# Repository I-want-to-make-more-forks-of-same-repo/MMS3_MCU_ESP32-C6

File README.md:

# MMS 3 ESP32 C6

## Project Status: **Ongoing**  
### Ver 1.0
**Design** ✅ — **Fabrication** ⏳ — **Assembly** ⏳ — **Bringup** ⏳ — **Testing** ⏳

Jak za 3 razem się udało, to za 4 też będzie git!

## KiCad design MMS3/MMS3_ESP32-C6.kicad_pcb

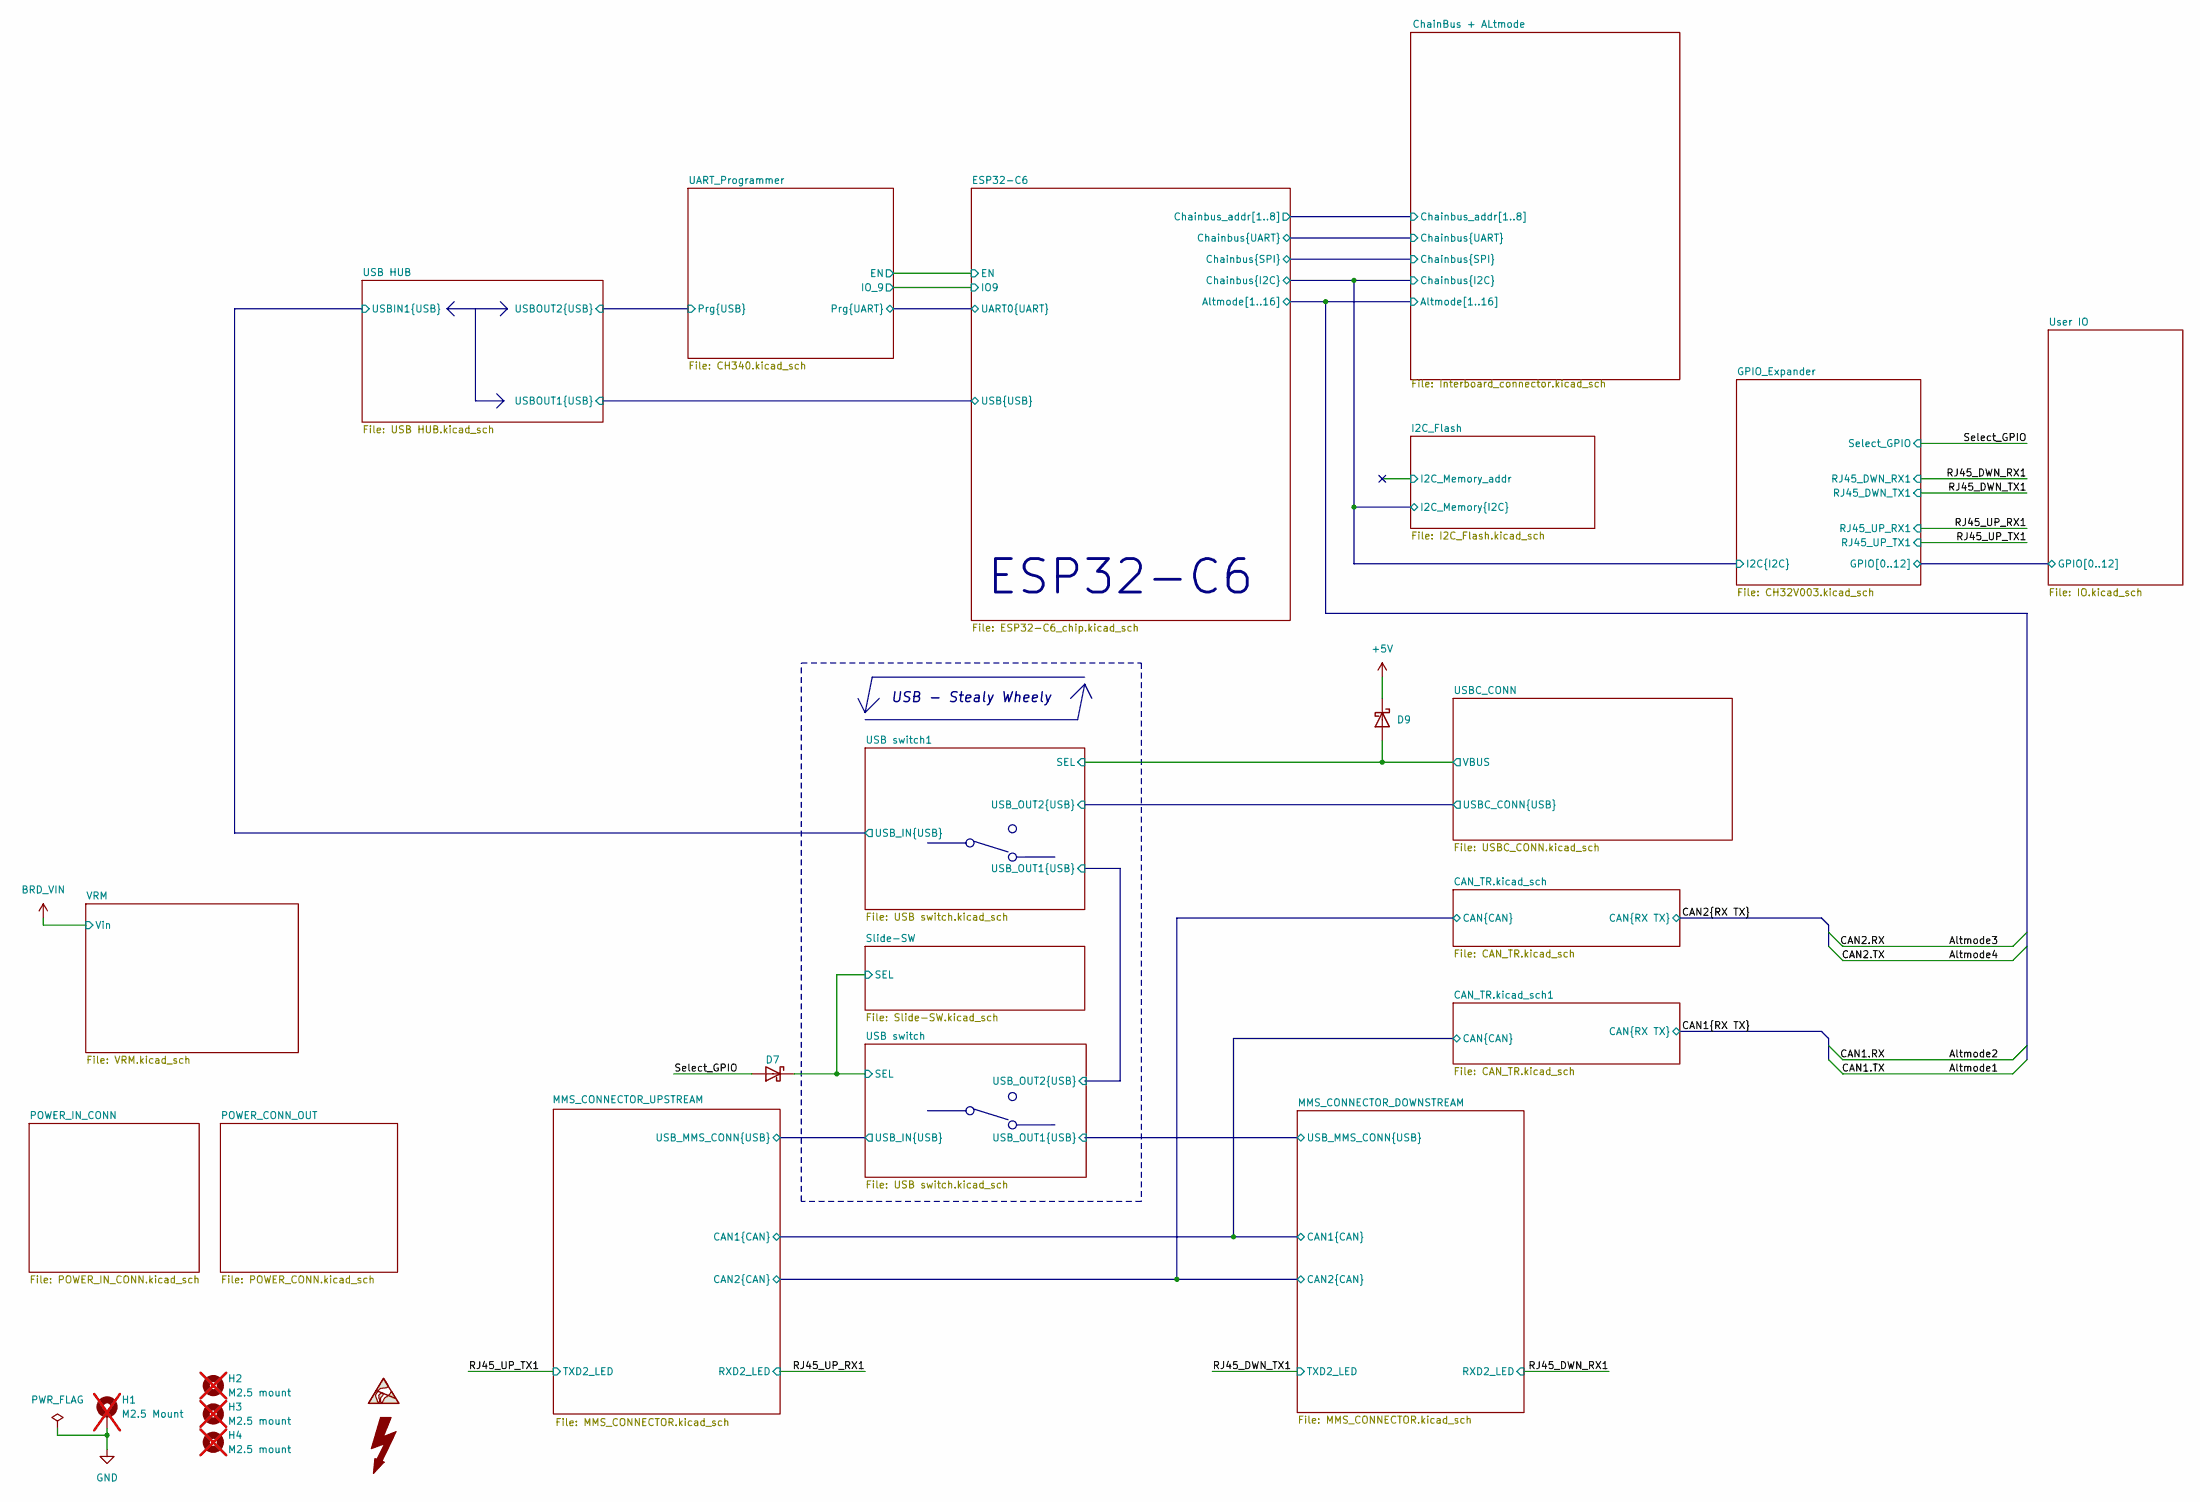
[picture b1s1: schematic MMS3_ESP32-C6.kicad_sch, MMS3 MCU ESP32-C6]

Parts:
D7, D9: 1N5819WS; D_SOD-323; Forward Voltage (Vf@If) 600mV@1A; Reverse Voltage (Vr) 40V; Part 1N5819WS; LCSC C191023
H1: M2.5 Mount; MountingHole_2.7mm_M2.5_DIN965_Pad_TopOnly; not fitted
H2, H3, H4: M2.5 mount; MountingHole_2.7mm_M2.5; not fitted

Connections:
+5V: D9.1; also elsewhere on the board
/Select_GPIO: D7.2; also elsewhere on the board
/Slide-SW/SEL: D7.1; also elsewhere on the board
/USBC_CONN/VBUS: D9.2; also elsewhere on the board
GND: H1.1 (1_1); also elsewhere on the board

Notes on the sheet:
USB - Stealy Wheely
ESP32-C6

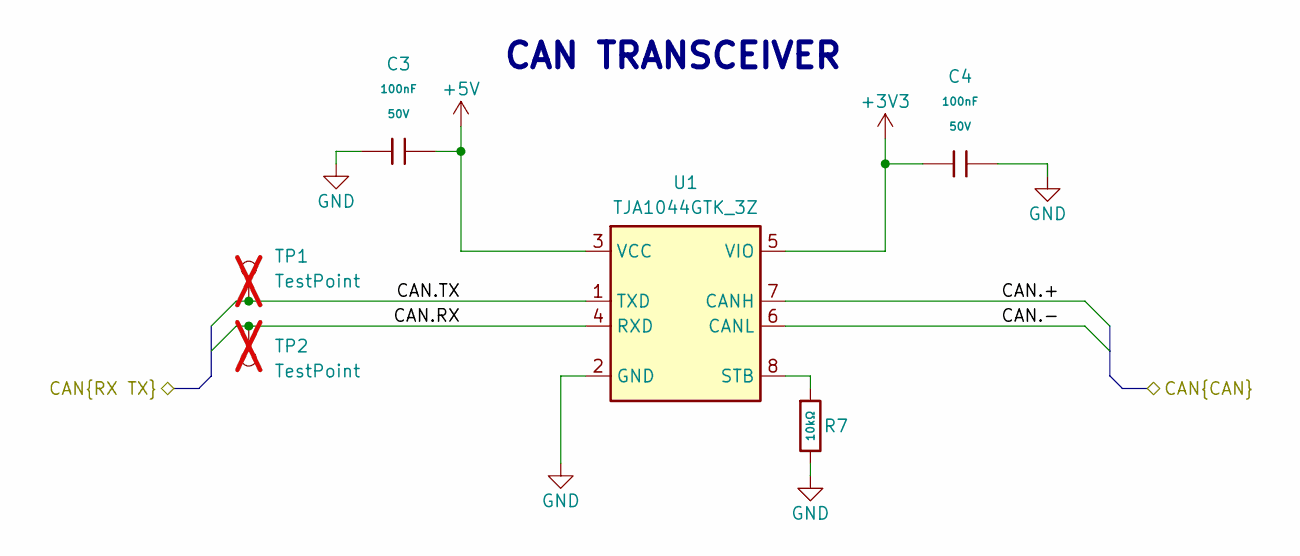
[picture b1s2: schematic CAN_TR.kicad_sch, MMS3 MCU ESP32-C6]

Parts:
C3, C4: 100nF; C_0402; Voltage Rated 50V; Tolerance ±10%; Part CL05B104KB54PNC; LCSC C307331
R7: 10kΩ; R_0402; Overload Voltage (Max) 50V; Tolerance ±1%; Part 0402WGF1002TCE; LCSC C25744
TP1, TP2: TestPoint; TestPoint_Pad_D1.0mm; not fitted
U1: TJA1044GTK_3Z; HVSON-8-1EP_3x3mm_P0.65mm_EP1.6x2.4mm; Manufacturer_Part_Number TJA1044GTK/3Z; LCSC C5215851

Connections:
+3V3: C4.1, U1.5 (VIO); also elsewhere on the board
+5V: C3.2, U1.3 (VCC); also elsewhere on the board
/CAN_TR.kicad_sch/CAN.+: U1.7 (CANH); also elsewhere on the board
/CAN_TR.kicad_sch/CAN.-: U1.6 (CANL); also elsewhere on the board
/ChainBus + ALtmode/Altmode3: TP2.1 (1_1), U1.4 (RXD); also elsewhere on the board
/ChainBus + ALtmode/Altmode4: TP1.1 (1_1), U1.1 (TXD); also elsewhere on the board
GND: C3.1, C4.2, R7.2, U1.2 (GND), U1.9 (EP); also elsewhere on the board
unnamed: R7.1, U1.8 (STB)

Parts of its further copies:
C6, C7: 100nF; C_0402; Voltage Rated 50V; Tolerance ±10%; Part CL05B104KB54PNC; LCSC C307331
R12: 10kΩ; R_0402; Overload Voltage (Max) 50V; Tolerance ±1%; Part 0402WGF1002TCE; LCSC C25744
TP3, TP4: TestPoint; TestPoint_Pad_D1.0mm; not fitted
U6: TJA1044GTK_3Z; HVSON-8-1EP_3x3mm_P0.65mm_EP1.6x2.4mm; Manufacturer_Part_Number TJA1044GTK/3Z; LCSC C5215851

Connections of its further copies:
+3V3: C7.1, U6.5 (VIO); also elsewhere on the board
+5V: C6.2, U6.3 (VCC); also elsewhere on the board
/CAN_TR.kicad_sch1/CAN.+: U6.7 (CANH); also elsewhere on the board
/CAN_TR.kicad_sch1/CAN.-: U6.6 (CANL); also elsewhere on the board
/ChainBus + ALtmode/Altmode1: TP3.1 (1_1), U6.1 (TXD); also elsewhere on the board
/ChainBus + ALtmode/Altmode2: TP4.1 (1_1), U6.4 (RXD); also elsewhere on the board
GND: C6.1, C7.2, R12.2, U6.2 (GND), U6.9 (EP); also elsewhere on the board
unnamed: R12.1, U6.8 (STB)

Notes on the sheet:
CAN TRANSCEIVER

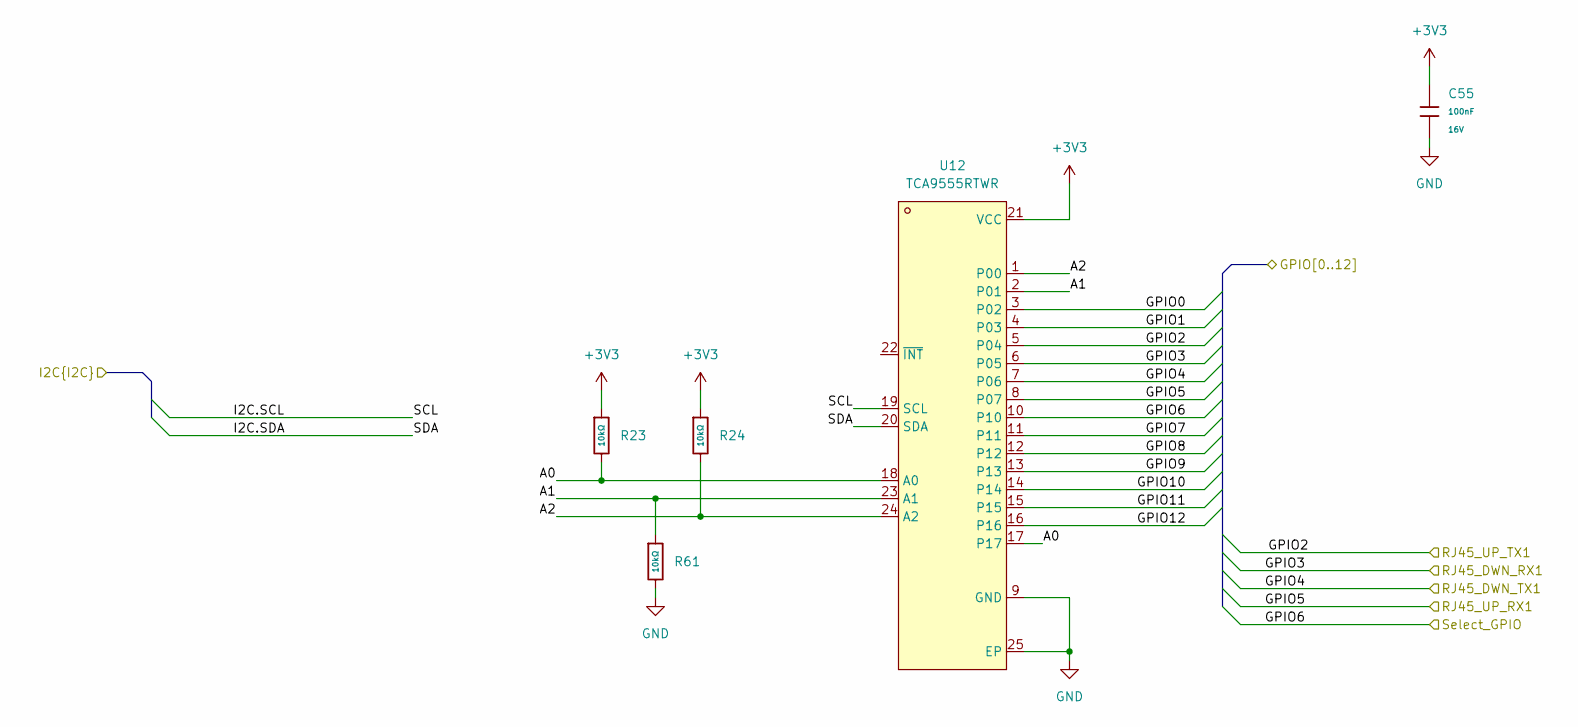
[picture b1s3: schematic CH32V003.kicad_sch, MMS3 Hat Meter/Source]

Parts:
C55: 100nF; C_0402; Voltage Rated 16V; Tolerance ±10%; Part CL05B104KO5NNNC; LCSC C1525
R23, R24, R61: 10kΩ; R_0402; Overload Voltage (Max) 50V; Tolerance ±1%; Part 0402WGF1002TCE; LCSC C25744
U12: TCA9555RTWR; HVQFN-24_L4.0-W4.0-P0.50-BL-EP2.6; MPN TCA9555RTWR(UMW); LCSC Part C42420609

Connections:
+3V3: C55.1, R23.1, R24.1, U12.21 (VCC); also elsewhere on the board
/ChainBus + ALtmode/Chainbus.SCL: U12.19 (SCL); also elsewhere on the board
/ChainBus + ALtmode/Chainbus.SDA: U12.20 (SDA); also elsewhere on the board
/GPIO_Expander/A0: R23.2, U12.17, U12.18 (A0)
/GPIO_Expander/A1: R61.1, U12.2 (P01), U12.23 (A1)
/GPIO_Expander/A2: R24.2, U12.1 (P00), U12.24 (A2)
/GPIO_Expander/GPIO0: U12.3 (P02); also elsewhere on the board
/GPIO_Expander/GPIO1: U12.4 (P03); also elsewhere on the board
/GPIO_Expander/GPIO7: U12.11
/GPIO_Expander/GPIO8: U12.12; also elsewhere on the board
/GPIO_Expander/GPIO9: U12.13; also elsewhere on the board
/GPIO_Expander/GPIO10: U12.14; also elsewhere on the board
/GPIO_Expander/GPIO11: U12.15
/GPIO_Expander/GPIO12: U12.16
/RJ45_DWN_RX1: U12.6 (P05); also elsewhere on the board
/RJ45_DWN_TX1: U12.7 (P06); also elsewhere on the board
/RJ45_UP_RX1: U12.8 (P07); also elsewhere on the board
/RJ45_UP_TX1: U12.5 (P04); also elsewhere on the board
/Select_GPIO: U12.10; also elsewhere on the board
GND: C55.2, R61.2, U12.9 (GND), U12.25 (EP); also elsewhere on the board

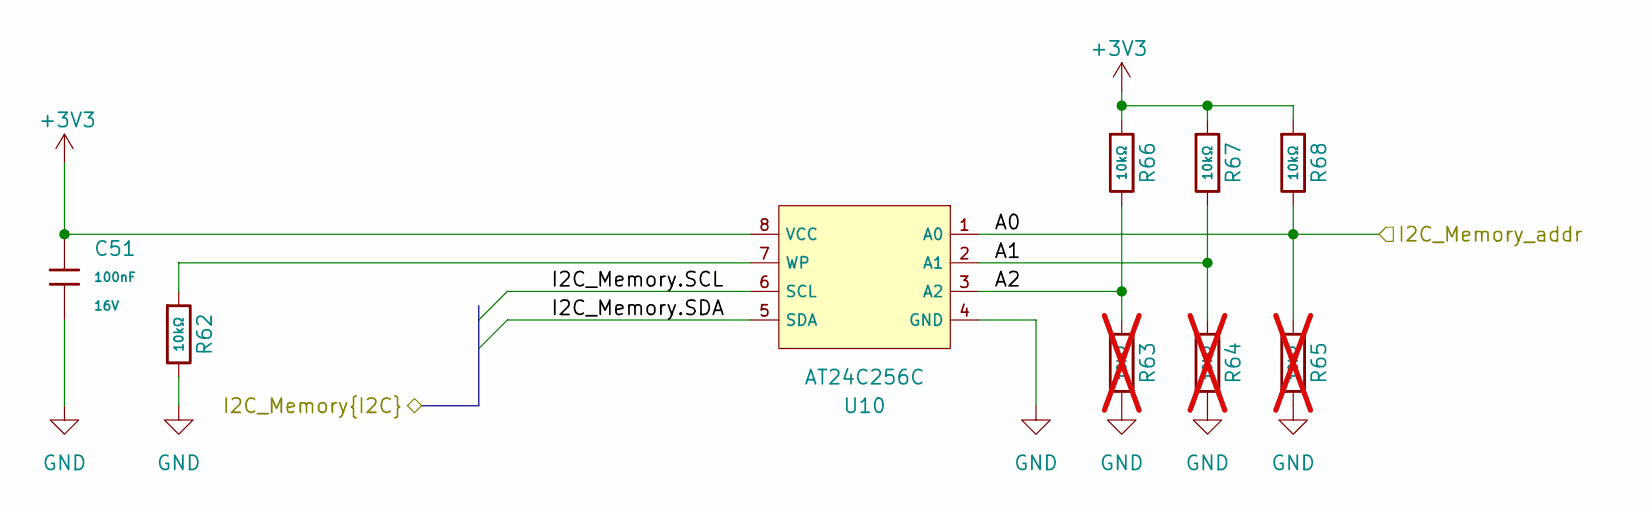
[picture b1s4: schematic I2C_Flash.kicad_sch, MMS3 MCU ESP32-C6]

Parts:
C51: 100nF; C_0402; Voltage Rated 16V; Tolerance ±10%; Part CL05B104KO5NNNC; LCSC C1525
R62, R66, R67, R68: 10kΩ; R_0402; Overload Voltage (Max) 50V; Tolerance ±1%; Part 0402WGF1002TCE; LCSC C25744
R63, R64, R65: 10kΩ; R_0402; Overload Voltage (Max) 50V; Tolerance ±1%; Part 0402WGF1002TCE; LCSC C25744; not fitted
U10: AT24C256C; SOIC-8_5.3x5.3mm_P1.27mm; Supply Voltage 1.7V~5.5V; Part AT24C256C-SSHL-T; LCSC C6482

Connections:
+3V3: C51.1, R66.1, R67.1, R68.1, U10.8 (VCC); also elsewhere on the board
/ChainBus + ALtmode/Chainbus.SCL: U10.6 (SCL); also elsewhere on the board
/ChainBus + ALtmode/Chainbus.SDA: U10.5 (SDA); also elsewhere on the board
/I2C_Flash/A0: R65.1, R68.2, U10.1 (A0)
/I2C_Flash/A1: R64.1, R67.2, U10.2 (A1)
/I2C_Flash/A2: R63.1, R66.2, U10.3 (A2)
GND: C51.2, R62.2, R63.2, R64.2, R65.2, U10.4 (GND); also elsewhere on the board
unnamed: R62.1, U10.7 (WP)

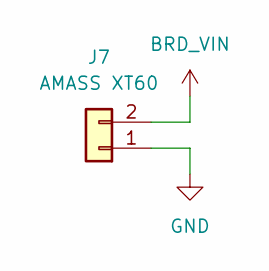
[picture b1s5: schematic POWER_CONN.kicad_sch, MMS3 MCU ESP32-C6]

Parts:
J7: AMASS XT60; AMASS_XT60PW-F_1x02_P7.20mm_Horizontal; LCSC C428722

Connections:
BRD_VIN: J7.2; also elsewhere on the board
GND: J7.1; also elsewhere on the board

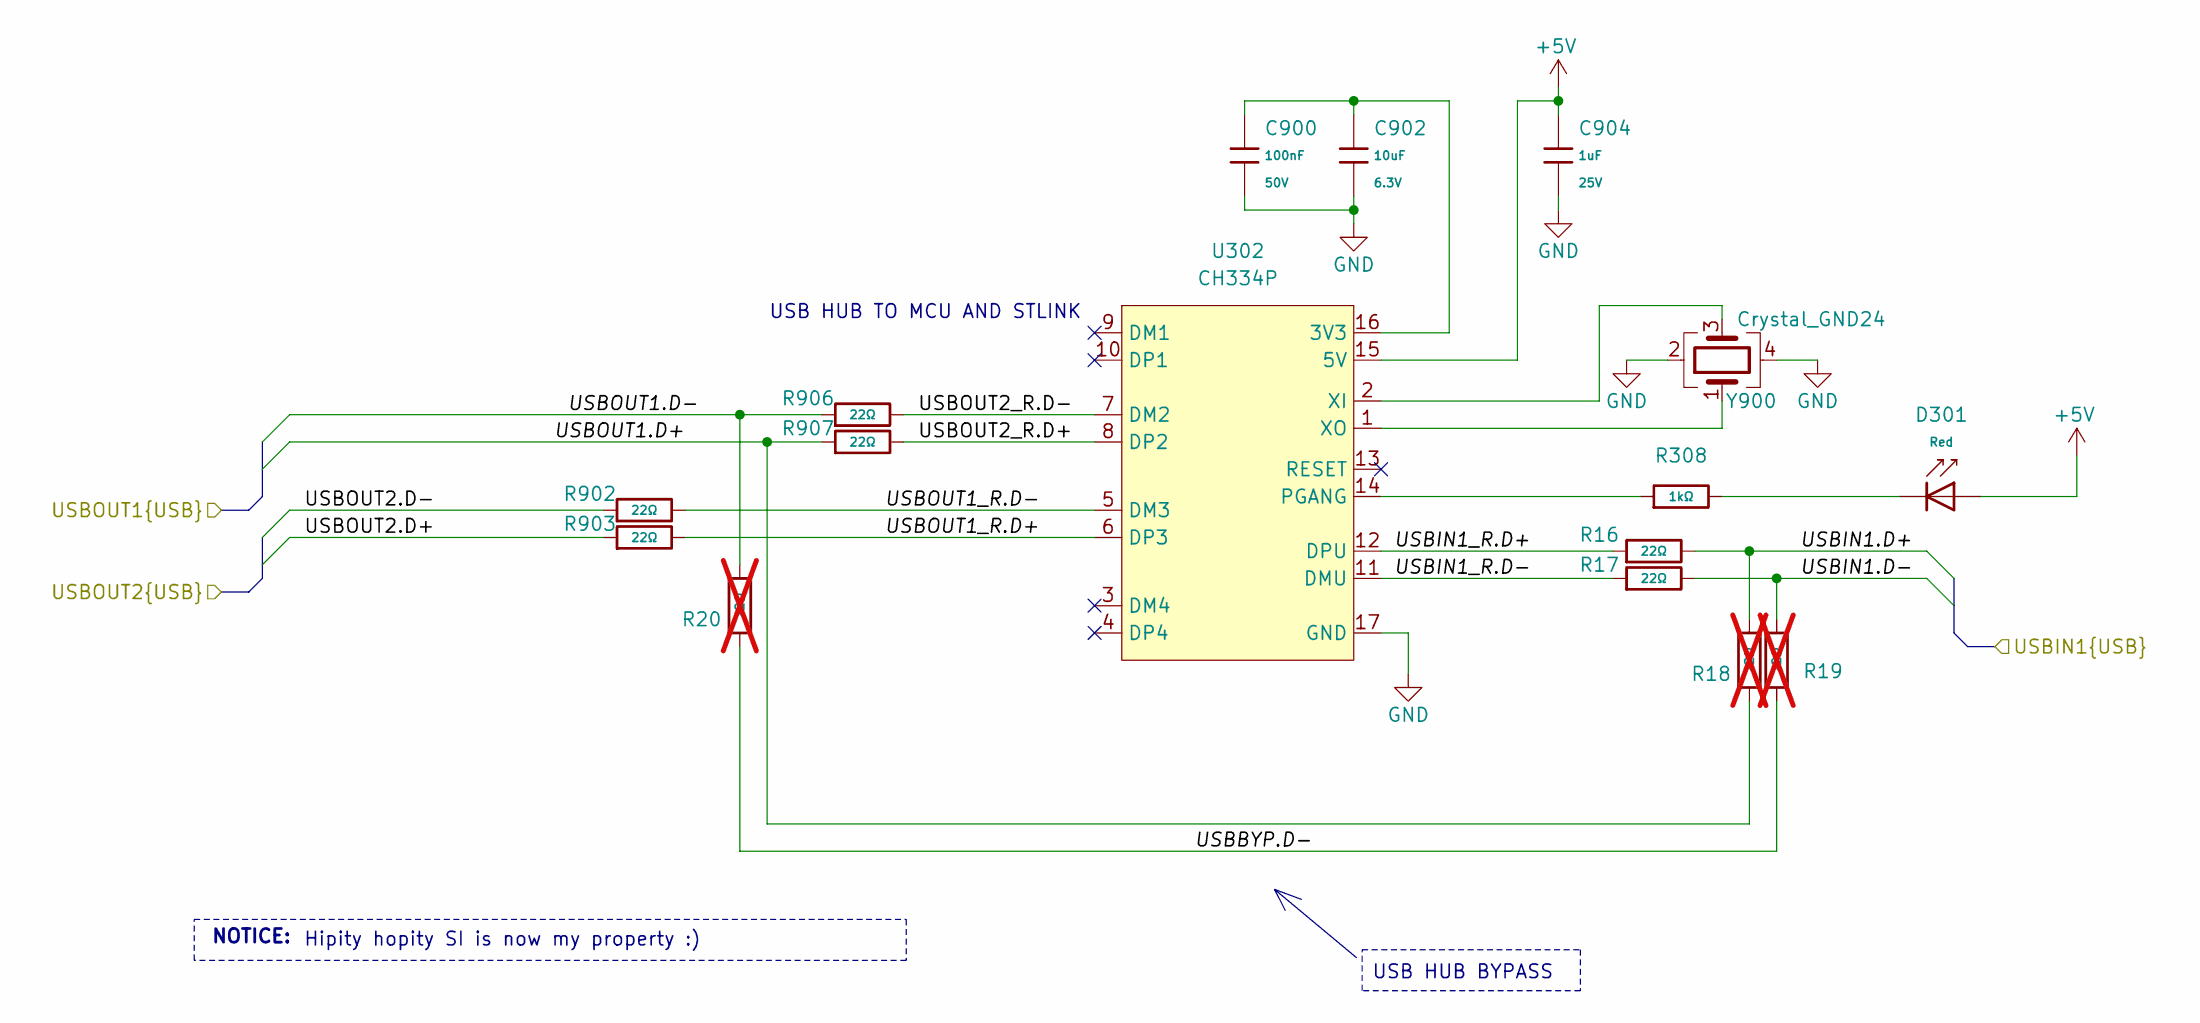
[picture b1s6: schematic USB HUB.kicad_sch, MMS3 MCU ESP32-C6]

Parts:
C900: 100nF; C_0402; Voltage Rated 50V; Tolerance ±10%; Part CL05B104KB54PNC; LCSC C307331
C902: 10uF; C_0402; Voltage Rated 6.3V; Tolerance ±20%; Part CL05A106MQ5NUNC; LCSC C15525
C904: 1uF; C_0402; Voltage Rated 25V; Tolerance ±10%; Part CL05A105KA5NQNC; LCSC C52923
D301: Red; D_0603; Part KT-0603R; LCSC C2286
R16, R17, R902, R903, R906, R907: 22Ω; R_0402; Overload Voltage (Max) 50V; Tolerance ±1%; Part 0402WGF220JTCE; LCSC C25092
R18, R19, R20: 22Ω; R_0402; Overload Voltage (Max) 50V; Tolerance ±1%; Part 0402WGF220JTCE; LCSC C25092; not fitted
R308: 1kΩ; R_0402; Overload Voltage (Max) 50V; Tolerance ±1%; Part 0402WGF1001TCE; LCSC C11702
U302: CH334P; QFN-16-1EP_3x3mm_P0.5mm_EP1.7x1.7mm; LCSC C5373042
Y900: Crystal_GND24; Crystal_SMD_3225-4Pin_3.2x2.5mm; LCSC C9002

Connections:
+5V: C904.1, D301.2, U302.15 (5V); also elsewhere on the board
/ESP32-C6/USB.D+: R18.1, R907.1; also elsewhere on the board
/ESP32-C6/USB.D-: R20.2, R906.1; also elsewhere on the board
/UART_Programmer/Prg.D+: R903.1; also elsewhere on the board
/UART_Programmer/Prg.D-: R902.1; also elsewhere on the board
/USB HUB/USBBYP.D-: R19.1, R20.1
/USB HUB/USBIN1.D+: R16.2, R18.2; also elsewhere on the board
/USB HUB/USBIN1.D-: R17.2, R19.2; also elsewhere on the board
/USB HUB/USBIN1_R.D+: R16.1, U302.12 (DPU)
/USB HUB/USBIN1_R.D-: R17.1, U302.11 (DMU)
/USB HUB/USBOUT1_R.D+: R903.2, U302.6 (DP3)
/USB HUB/USBOUT1_R.D-: R902.2, U302.5 (DM3)
/USB HUB/USBOUT2_R.D+: R907.2, U302.8 (DP2)
/USB HUB/USBOUT2_R.D-: R906.2, U302.7 (DM2)
GND: C900.2, C902.2, C904.2, U302.17 (GND), Y900.2, Y900.4; also elsewhere on the board
unnamed: D301.1, R308.2
unnamed: C900.1, C902.1, U302.16 (3V3)
unnamed: R308.1, U302.14 (PGANG)
unnamed: U302.2 (XI), Y900.3
unnamed: U302.1 (XO), Y900.1

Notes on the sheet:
NOTICE:
Hipity hopity SI is now my property :)
USB HUB TO MCU AND STLINK
USB HUB BYPASS

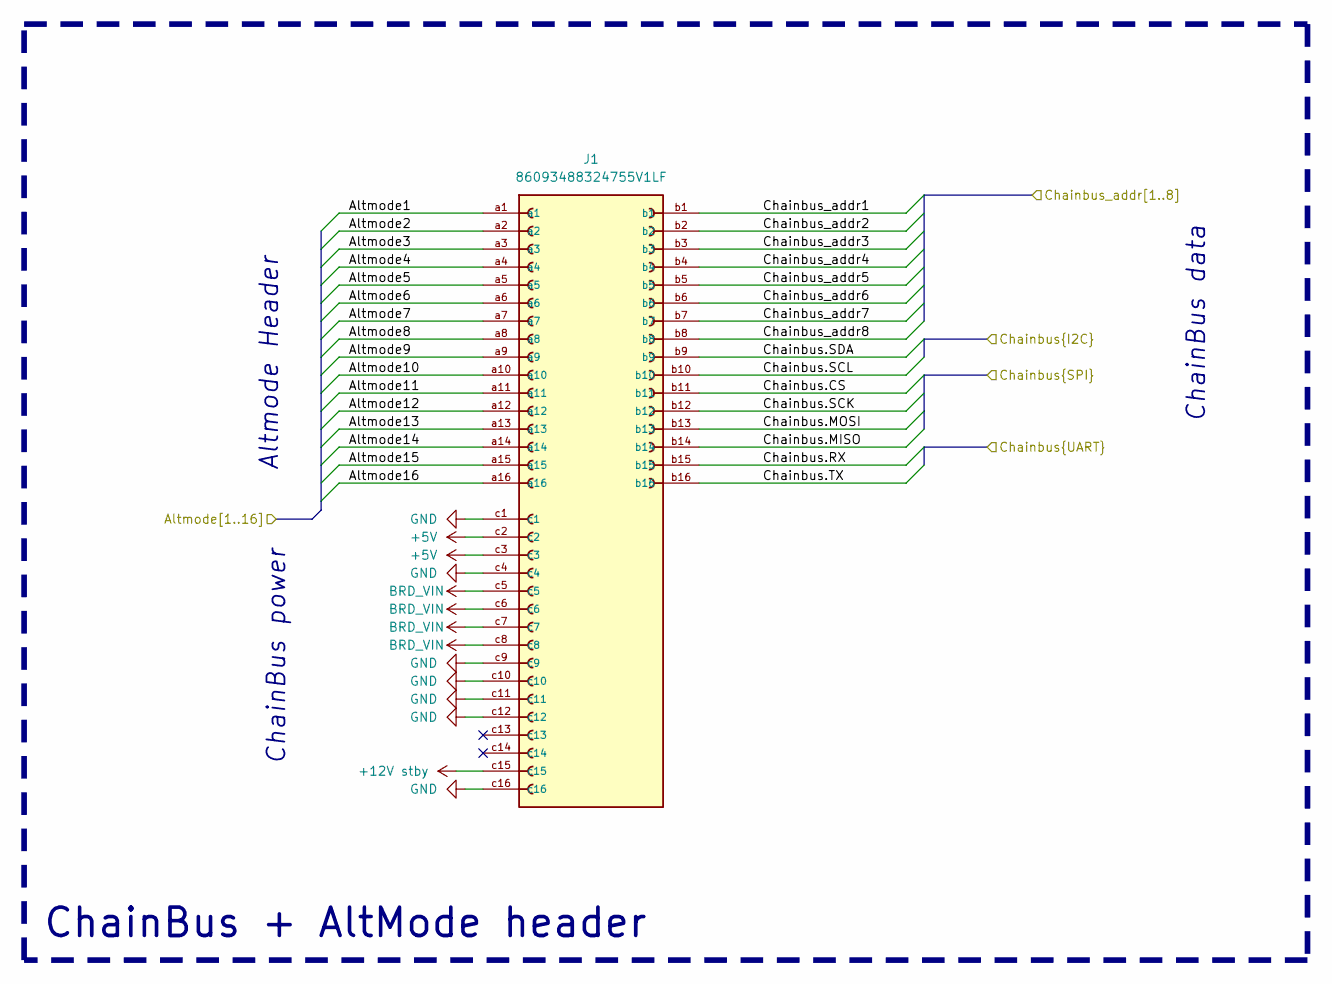
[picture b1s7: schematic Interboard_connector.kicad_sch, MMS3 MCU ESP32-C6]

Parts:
J1: 86093488324755V1LF; DIN41612_C2_3x16_Female_Vertical_THT; PARTREV C; LCSC C5173373

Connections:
+5V: J1.c2, J1.c3; also elsewhere on the board
+12V stby: J1.c15; also elsewhere on the board
/ChainBus + ALtmode/Altmode1: J1.a1; also elsewhere on the board
/ChainBus + ALtmode/Altmode2: J1.a2; also elsewhere on the board
/ChainBus + ALtmode/Altmode3: J1.a3; also elsewhere on the board
/ChainBus + ALtmode/Altmode4: J1.a4; also elsewhere on the board
/ChainBus + ALtmode/Altmode5: J1.a5
/ChainBus + ALtmode/Altmode6: J1.a6
/ChainBus + ALtmode/Altmode7: J1.a7
/ChainBus + ALtmode/Altmode8: J1.a8
/ChainBus + ALtmode/Altmode9: J1.a9
/ChainBus + ALtmode/Altmode10: J1.a10
/ChainBus + ALtmode/Altmode11: J1.a11
/ChainBus + ALtmode/Altmode12: J1.a12
/ChainBus + ALtmode/Altmode13: J1.a13
/ChainBus + ALtmode/Altmode14: J1.a14
/ChainBus + ALtmode/Altmode15: J1.a15
/ChainBus + ALtmode/Altmode16: J1.a16
/ChainBus + ALtmode/Chainbus.CS: J1.b11; also elsewhere on the board
/ChainBus + ALtmode/Chainbus.MISO: J1.b14; also elsewhere on the board
/ChainBus + ALtmode/Chainbus.MOSI: J1.b13; also elsewhere on the board
/ChainBus + ALtmode/Chainbus.RX: J1.b15; also elsewhere on the board
/ChainBus + ALtmode/Chainbus.SCK: J1.b12; also elsewhere on the board
/ChainBus + ALtmode/Chainbus.SCL: J1.b10; also elsewhere on the board
/ChainBus + ALtmode/Chainbus.SDA: J1.b9; also elsewhere on the board
/ChainBus + ALtmode/Chainbus.TX: J1.b16; also elsewhere on the board
/ChainBus + ALtmode/Chainbus_addr1: J1.b1; also elsewhere on the board
/ChainBus + ALtmode/Chainbus_addr2: J1.b2; also elsewhere on the board
/ChainBus + ALtmode/Chainbus_addr3: J1.b3; also elsewhere on the board
/ChainBus + ALtmode/Chainbus_addr4: J1.b4; also elsewhere on the board
/ChainBus + ALtmode/Chainbus_addr5: J1.b5; also elsewhere on the board
/ChainBus + ALtmode/Chainbus_addr6: J1.b6; also elsewhere on the board
/ChainBus + ALtmode/Chainbus_addr7: J1.b7; also elsewhere on the board
/ChainBus + ALtmode/Chainbus_addr8: J1.b8; also elsewhere on the board
BRD_VIN: J1.c5, J1.c6, J1.c7, J1.c8; also elsewhere on the board
GND: J1.c1, J1.c4, J1.c9, J1.c10, J1.c11, J1.c12, J1.c16; also elsewhere on the board

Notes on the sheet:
ChainBus data
ChainBus power
Altmode Header
ChainBus + AltMode header

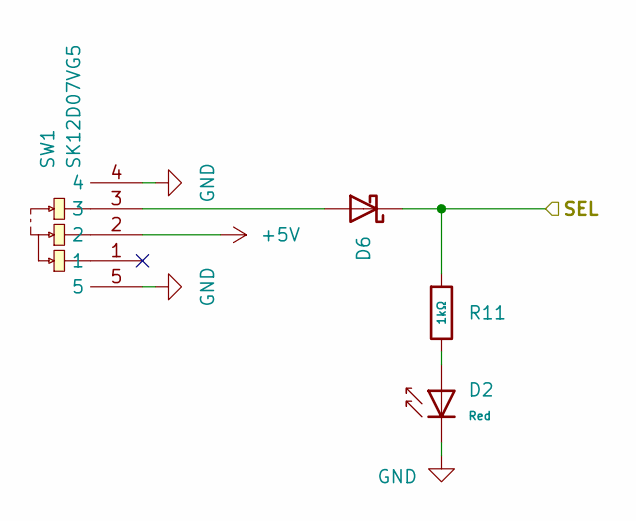
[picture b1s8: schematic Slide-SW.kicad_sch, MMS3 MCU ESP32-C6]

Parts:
D2: Red; D_0603; Part KT-0603R; LCSC C2286
D6: 1N5819WS; D_SOD-323; Forward Voltage (Vf@If) 600mV@1A; Reverse Voltage (Vr) 40V; Part 1N5819WS; LCSC C191023
R11: 1kΩ; R_0402; Overload Voltage (Max) 50V; Tolerance ±1%; Part 0402WGF1001TCE; LCSC C11702
SW1: SK12D07VG5; SW-TH_SK12D07VG5-1; MPN SK12D07VG5; LCSC Part C431548

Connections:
+5V: SW1.2; also elsewhere on the board
/Slide-SW/SEL: D6.1, R11.1; also elsewhere on the board
GND: D2.1, SW1.4, SW1.5; also elsewhere on the board
unnamed: D2.2, R11.2
unnamed: D6.2, SW1.3

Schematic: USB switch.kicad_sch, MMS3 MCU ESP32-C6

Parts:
C5: 100nF; C_0402; Voltage Rated 50V; Tolerance ±10%; Part CL05B104KB54PNC; LCSC C307331
R8, R10: 10kΩ; R_0402; Overload Voltage (Max) 50V; Tolerance ±1%; Part 0402WGF1002TCE; LCSC C25744
R9: 22kΩ; R_0402; Overload Voltage (Max) 50V; Tolerance ±1%; Part 0402WGF2202TCE; LCSC C25768
U3: FSUSB42UMX; UQFN-10_1.4x1.8mm_P0.4mm; PARTREV 1.25; LCSC C11145

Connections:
+3V3: C5.1, U3.9 (VCC); also elsewhere on the board
/MMS_CONNECTOR_DOWNSTREAM/USB_MMS_CONN.D+: U3.5 (HSD1+); also elsewhere on the board
/MMS_CONNECTOR_DOWNSTREAM/USB_MMS_CONN.D-: U3.4 (HSD1-); also elsewhere on the board
/MMS_CONNECTOR_UPSTREAM/USB_MMS_CONN.D+: U3.1 (D+); also elsewhere on the board
/MMS_CONNECTOR_UPSTREAM/USB_MMS_CONN.D-: U3.2 (D-); also elsewhere on the board
/Slide-SW/SEL: R8.1; also elsewhere on the board
/USB switch/USB_OUT2.D+: U3.7 (HSD2+); also elsewhere on the board
/USB switch/USB_OUT2.D-: U3.6 (HSD2-); also elsewhere on the board
GND: C5.2, R9.2, R10.2, U3.3 (GND); also elsewhere on the board
unnamed: R8.2, R9.1, U3.10 (SEL)
unnamed: R10.1, U3.8 (~OE)

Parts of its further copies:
C8: 100nF; C_0402; Voltage Rated 50V; Tolerance ±10%; Part CL05B104KB54PNC; LCSC C307331
R13, R15: 10kΩ; R_0402; Overload Voltage (Max) 50V; Tolerance ±1%; Part 0402WGF1002TCE; LCSC C25744
R14: 22kΩ; R_0402; Overload Voltage (Max) 50V; Tolerance ±1%; Part 0402WGF2202TCE; LCSC C25768
U7: FSUSB42UMX; UQFN-10_1.4x1.8mm_P0.4mm; PARTREV 1.25; LCSC C11145

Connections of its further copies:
+3V3: C8.1, U7.9 (VCC); also elsewhere on the board
/USB HUB/USBIN1.D+: U7.1 (D+); also elsewhere on the board
/USB HUB/USBIN1.D-: U7.2 (D-); also elsewhere on the board
/USB switch1/USB_OUT2.D+: U7.7 (HSD2+); also elsewhere on the board
/USB switch1/USB_OUT2.D-: U7.6 (HSD2-); also elsewhere on the board
/USB switch/USB_OUT2.D+: U7.5 (HSD1+); also elsewhere on the board
/USB switch/USB_OUT2.D-: U7.4 (HSD1-); also elsewhere on the board
/USBC_CONN/VBUS: R13.1; also elsewhere on the board
GND: C8.2, R14.2, R15.2, U7.3 (GND); also elsewhere on the board
unnamed: R13.2, R14.1, U7.10 (SEL)
unnamed: R15.1, U7.8 (~OE)

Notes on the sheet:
ALTERNATE PART: EnergyMath EMS3900 1.9Ω 800MHz 2:1 USB QFN-10L(1.4x1.8) Analog Switches - Special Purpose ROHS PIN COMPATIBLE
NOTE:

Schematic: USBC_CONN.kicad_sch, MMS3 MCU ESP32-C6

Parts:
C12: 100nF; C_0402; Voltage Rated 16V; Tolerance ±10%; Part CL05B104KO5NNNC; LCSC C1525
C13: 10nF; C_0402; Voltage Rated 50V; Tolerance ±10%; Part CL05B103KB5NNNC; LCSC C15195
J4: USB_C_Receptacle_USB2.0_16P; USB_C_Receptacle_GCT_USB4105-xx-A_16P_TopMnt_Horizontal; LCSC C165948
R25, R26: 5.1kΩ; R_0402; Overload Voltage (Max) 50V; Tolerance ±1%; Part 0402WGF5101TCE; LCSC C25905
R27: 33kΩ; R_0402; Overload Voltage (Max) 50V; Tolerance ±1%; Part 0402WGF3302TCE; LCSC C25779
U9: TPD2EUSB30DRTR-TP; SOT-723; LCSC C2844720

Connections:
/USB switch1/USB_OUT2.D+: J4.A6 (D+), J4.B6 (D+), U9.2; also elsewhere on the board
/USB switch1/USB_OUT2.D-: J4.A7 (D-), J4.B7 (D-), U9.1; also elsewhere on the board
/USBC_CONN/CC1: J4.A5 (CC1), R25.1
/USBC_CONN/CC2: J4.B5 (CC2), R26.1
/USBC_CONN/VBUS: C12.1, J4.A4 (VBUS), J4.A9 (VBUS), J4.B4 (VBUS), J4.B9 (VBUS); also elsewhere on the board
GND: C12.2, C13.2, J4.A1 (GND), J4.A12 (GND), J4.B1 (GND), J4.B12 (GND), R25.2, R26.2, R27.2, U9.3; also elsewhere on the board
unnamed: C13.1, J4.SH (SHIELD), R27.1

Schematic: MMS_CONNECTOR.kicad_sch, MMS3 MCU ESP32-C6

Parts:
C1: 10nF; C_0402; Voltage Rated 50V; Tolerance ±10%; Part CL05B103KB5NNNC; LCSC C15195
J8: RJ45_LED_Shielded; RJ45_Amphenol_RJHSE538X; LCSC C7501824; not fitted
R1, R3: 220Ω; R_0402; Overload Voltage (Max) 50V; Tolerance ±1%; Part 0402WGF2200TCE; LCSC C25091
R5: 33kΩ; R_0402; Overload Voltage (Max) 50V; Tolerance ±1%; Part 0402WGF3302TCE; LCSC C25779
U4: TPD2EUSB30DRTR-TP; SOT-723; LCSC C2844720

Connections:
+12V stby: J8.6; also elsewhere on the board
/CAN_TR.kicad_sch1/CAN.+: J8.2; also elsewhere on the board
/CAN_TR.kicad_sch1/CAN.-: J8.1; also elsewhere on the board
/CAN_TR.kicad_sch/CAN.+: J8.5; also elsewhere on the board
/CAN_TR.kicad_sch/CAN.-: J8.4; also elsewhere on the board
/MMS_CONNECTOR_DOWNSTREAM/USB_MMS_CONN.D+: J8.8, U4.2; also elsewhere on the board
/MMS_CONNECTOR_DOWNSTREAM/USB_MMS_CONN.D-: J8.7, U4.1; also elsewhere on the board
/RJ45_DWN_RX1: R3.2; also elsewhere on the board
/RJ45_DWN_TX1: R1.2; also elsewhere on the board
GND: C1.2, J8.3, J8.9, J8.11, R5.2, U4.3; also elsewhere on the board
unnamed: C1.1, J8.SH, R5.1
unnamed: J8.10, R1.1
unnamed: J8.12, R3.1

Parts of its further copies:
C2: 10nF; C_0402; Voltage Rated 50V; Tolerance ±10%; Part CL05B103KB5NNNC; LCSC C15195
J9: RJ45_LED_Shielded; RJ45_Amphenol_RJHSE538X; LCSC C7501824; not fitted
R2, R4: 220Ω; R_0402; Overload Voltage (Max) 50V; Tolerance ±1%; Part 0402WGF2200TCE; LCSC C25091
R6: 33kΩ; R_0402; Overload Voltage (Max) 50V; Tolerance ±1%; Part 0402WGF3302TCE; LCSC C25779
U5: TPD2EUSB30DRTR-TP; SOT-723; LCSC C2844720

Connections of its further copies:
+12V stby: J9.6; also elsewhere on the board
/CAN_TR.kicad_sch1/CAN.+: J9.2; also elsewhere on the board
/CAN_TR.kicad_sch1/CAN.-: J9.1; also elsewhere on the board
/CAN_TR.kicad_sch/CAN.+: J9.5; also elsewhere on the board
/CAN_TR.kicad_sch/CAN.-: J9.4; also elsewhere on the board
/MMS_CONNECTOR_UPSTREAM/USB_MMS_CONN.D+: J9.8, U5.2; also elsewhere on the board
/MMS_CONNECTOR_UPSTREAM/USB_MMS_CONN.D-: J9.7, U5.1; also elsewhere on the board
/RJ45_UP_RX1: R4.2; also elsewhere on the board
/RJ45_UP_TX1: R2.2; also elsewhere on the board
GND: C2.2, J9.3, J9.9, J9.11, R6.2, U5.3; also elsewhere on the board
unnamed: C2.1, J9.SH, R6.1
unnamed: J9.10, R2.1
unnamed: J9.12, R4.1

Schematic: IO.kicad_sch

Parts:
KEY1: TL2243; KEY-TH_TL2243; MPN TL2243; LCSC Part C273515
LED1, LED2: FixLed307; not fitted
R30, R31, R32, R35: 1kΩ; R_0402; Overload Voltage (Max) 50V; Tolerance ±1%; Part 0402WGF1001TCE; LCSC C11702
R40, R41: 10kΩ; R_0402; Overload Voltage (Max) 50V; Tolerance ±1%; Part 0402WGF1002TCE; LCSC C25744

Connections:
+3V3: KEY1.3, KEY1.4, R31.1; also elsewhere on the board
/GPIO_Expander/GPIO0: R32.1; also elsewhere on the board
/GPIO_Expander/GPIO1: R35.1; also elsewhere on the board
/GPIO_Expander/GPIO8: R30.1; also elsewhere on the board
/GPIO_Expander/GPIO9: KEY1.1, R41.1; also elsewhere on the board
/GPIO_Expander/GPIO10: KEY1.2, R40.1; also elsewhere on the board
GND: KEY1.0, LED1.2, LED1.4, LED2.2, LED2.4, R40.2, R41.2; also elsewhere on the board
unnamed: LED1.1, R31.2
unnamed: LED1.3, R30.2
unnamed: LED2.1, R35.2
unnamed: LED2.3, R32.2

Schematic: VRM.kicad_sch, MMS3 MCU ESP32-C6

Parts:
C9, C10: 100nF; C_0603; Voltage Rated 50V; Tolerance ±10%; Part CC0603KRX7R9BB104; LCSC C14663
C30, C31, C32, C33, C34, C35: 10uF; C_0805; Voltage Rated 50V; Tolerance ±10%; Part GRM21BR61H106KE43L; LCSC C440198
C38, C39: 220nF; C_0805; Voltage Rated 50V; Tolerance ±10%; Part CL21B224KBFNNNE; LCSC C5378
C40: 100nF; C_0805; Voltage Rated 100V; Tolerance ±10%; Part CL21B104KCFNNNE; LCSC C28233
C41, C42, C45, C46, C47, C48: 22uF; C_0805; Voltage Rated 25V; Tolerance ±20%; Part CL21A226MAQNNNE; LCSC C45783
C43: 47pF; C_0402; Voltage Rated 50V; Tolerance ±5%; Part 0402CG470J500NT; LCSC C1567
C44: 4.7nF; C_0402; Voltage Rated 50V; Tolerance ±10%; Part 0402B472K500NT; LCSC C1538
C49, C50: 100uF; CP_Elec_10x10; MPN VZH101M1KTR-1010; LCSC C249838
D1: SMF58CA; D_SOD-123FL; Clamping Voltage 93.6V; Voltage - Breakdown 71.2V; Part SMF58CA; LCSC C42371753
D3, D4: SS510B; D_SMB; Forward Voltage (Vf@If) 0.85V@5.0A; Reverse Voltage (Vr) 100V; Part SS510B; LCSC C7420368
L1: YSPI1050-100M; L_Sunlord_MWSA1005S; LCSC C497897
R21: 47kΩ; R_0402; Overload Voltage (Max) 50V; Tolerance ±1%; Part 0402WGF4702TCE; LCSC C25792
R33, R34: 24.9kΩ; R_0402; Overload Voltage (Max) 50V; Tolerance ±1%; Part 0402WGF2402TCE; LCSC C25874
R37: 8.2kΩ; R_0402; Overload Voltage (Max) 50V; Tolerance ±1%; Part 0402WGF8201TCE; LCSC C25924
R38: 12kΩ; R_0402; Overload Voltage (Max) 50V; Tolerance ±1%; Part 0402WGF1202TCE; LCSC C25752
R39: 240kΩ; R_0603; Overload Voltage (Max) 75V; Tolerance ±1%; Part 0603WAF2403T5E; LCSC C4197
TP16, TP17, TP18, TP19, TP20: TestPoint; TestPoint_Pad_D1.0mm; not fitted
U2: TPS54560BDDA; Texas_R-PDSO-G8_EP2.95x4.9mm_Mask2.4x3.1mm_ThermalVias; LCSC C1850354
U15: AMS1117-3.3; SOT-223-3_TabPin2

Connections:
+3V3: C10.1, C48.1, U15.2 (VO); also elsewhere on the board
+5V: C9.1, C50.1, D4.1, U15.3 (VI); also elsewhere on the board
/VRM/Cap_protec: C30.2, C31.1, C32.2, C33.1, C34.2, C35.1, C38.2, C39.1, R33.2, R34.1
BRD_VIN: C30.1, C32.1, C34.1, C38.1, C49.1, D1.1, R33.1, TP16.1 (1_1), U2.2 (VIN); also elsewhere on the board
GND: C9.2, C10.2, C31.2, C33.2, C35.2, C39.2, C41.2, C42.2, C43.2, C44.2, C45.2, C46.2, C47.2, C48.2, C49.2, C50.2, D1.2, D3.2, R34.2, R37.2, R39.2, U2.7 (GND), U2.9 (GND), U15.1 (GND); also elsewhere on the board
unnamed: C41.1, C42.1, C45.1, C46.1, C47.1, D4.2, L1.2, R21.1, TP19.1 (1_1)
unnamed: C44.1, R38.2
unnamed: C40.2, U2.1 (BOOT)
unnamed: C43.1, R38.1, TP17.1 (1_1), U2.6 (COMP)
unnamed: R21.2, R37.1, TP18.1 (1_1), U2.5 (FB)
unnamed: R39.1, TP20.1 (1_1), U2.4 (RT/CLK)
unnamed: C40.1, D3.1, L1.1, U2.8 (SW)

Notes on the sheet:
saved for kebab on that one alone
INFORMATION
KEEP CRIPPAGE DISTANCE 1.26MM MIN!
~5.4V
Thats not sketch ... thats BOM-bastic!
HUMAN NUMBER GENERATOR OUTPUT
RANDOM NUMBER GENERATOR OUTPUT
~5V
60V MAX
IEC 60664-1 Material Group III (CTI < 400; typical FR-4 = IIIa): 1.25 mm

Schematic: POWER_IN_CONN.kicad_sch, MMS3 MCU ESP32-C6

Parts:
J2: AMASS XT60; AMASS_XT60PW-M_1x02_P7.20mm_Horizontal; LCSC C98732

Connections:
BRD_VIN: J2.2; also elsewhere on the board
GND: J2.1; also elsewhere on the board
